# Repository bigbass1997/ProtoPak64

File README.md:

### Description
The ProtoPak64 is a breakout and prototyping PCB for the accessory pak port found on the bottom of N64 controllers.

Latest gerber files can be found in `/hardware/fab/protopak64-2024-06-19.zip`.

### JLCPCB Ordering
Single PCB, 1.2mm thickness, HASL finish (or better), 1oz copper weight, and using a specified location for the order number. PCB Color can be anything. Use default for remaining options.

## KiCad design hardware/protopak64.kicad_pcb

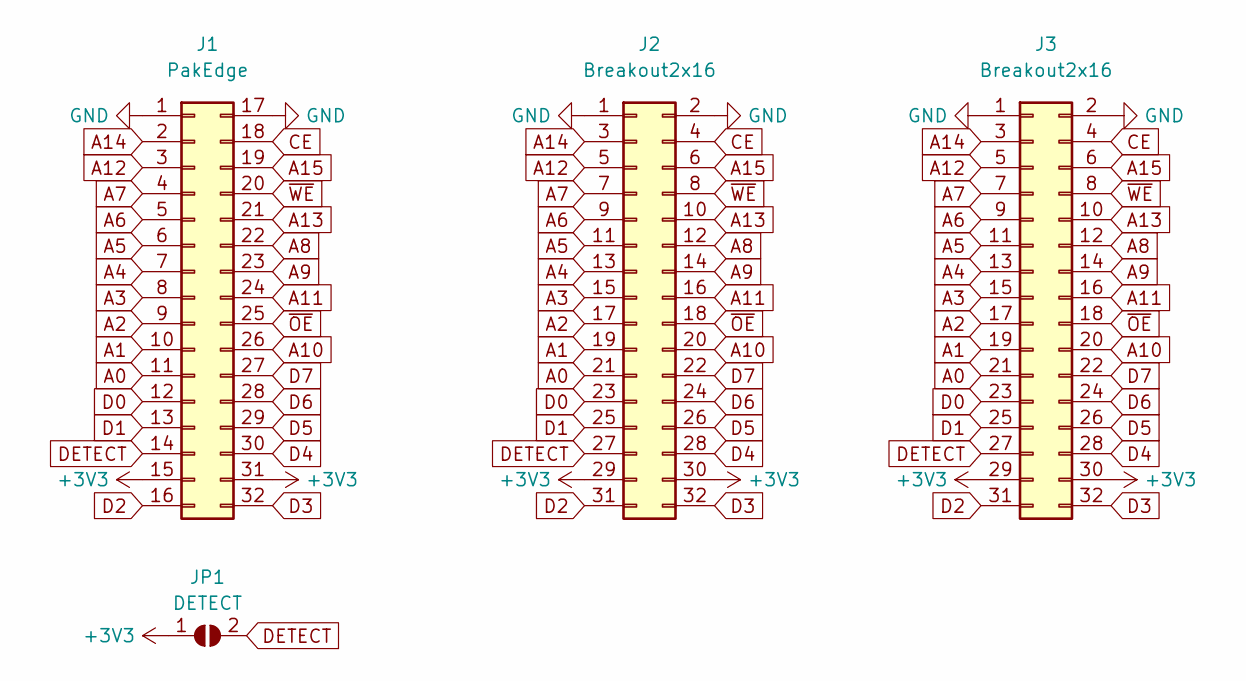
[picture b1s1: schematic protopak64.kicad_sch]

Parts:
J1: PakEdge; PakEdgeConnector
J2, J3: Breakout2x16; PinHeader_2x16_P2.54mm_Vertical
JP1: DETECT; SolderJumper-2_P1.3mm_Open_TrianglePad1.0x1.5mm

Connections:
+3V3: J1.15, J1.31, J2.29, J2.30, J3.29, J3.30, JP1.1 (A)
A0: J1.11, J2.21, J3.21
A1: J1.10, J2.19, J3.19
A2: J1.9, J2.17, J3.17
A3: J1.8, J2.15, J3.15
A4: J1.7, J2.13, J3.13
A5: J1.6, J2.11, J3.11
A6: J1.5, J2.9, J3.9
A7: J1.4, J2.7, J3.7
A8: J1.22, J2.12, J3.12
A9: J1.23, J2.14, J3.14
A10: J1.26, J2.20, J3.20
A11: J1.24, J2.16, J3.16
A12: J1.3, J2.5, J3.5
A13: J1.21, J2.10, J3.10
A14: J1.2, J2.3, J3.3
A15: J1.19, J2.6, J3.6
CE: J1.18, J2.4, J3.4
D0: J1.12, J2.23, J3.23
D1: J1.13, J2.25, J3.25
D2: J1.16, J2.31, J3.31
D3: J1.32, J2.32, J3.32
D4: J1.30, J2.28, J3.28
D5: J1.29, J2.26, J3.26
D6: J1.28, J2.24, J3.24
D7: J1.27, J2.22, J3.22
DETECT: J1.14, J2.27, J3.27, JP1.2 (B)
GND: J1.1, J1.17, J2.1, J2.2, J3.1, J3.2
~OE: J1.25, J2.18, J3.18
~WE: J1.20, J2.8, J3.8

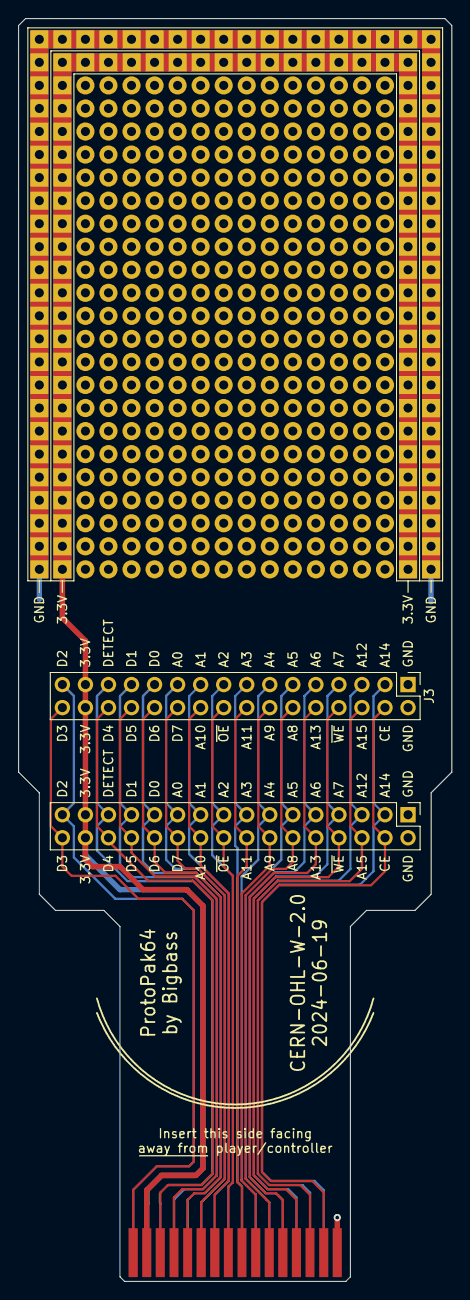
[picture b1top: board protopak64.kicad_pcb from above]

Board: 2 copper layers, 47.8 x 139.2 mm, 4 parts (1 on the bottom side), 30 nets.

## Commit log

2022-07-07 Initial commit.
2022-07-07 Update README.
2022-07-07 Update JLCPCB ordering options.
2024-06-19 Extended hole grid, added second set of headers, and adjusted orientation details.

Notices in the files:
README.md:
License: CERN OHL-W-V2
hardware/protopak64.kicad_pcb:
CERN-OHL-W-2.0
